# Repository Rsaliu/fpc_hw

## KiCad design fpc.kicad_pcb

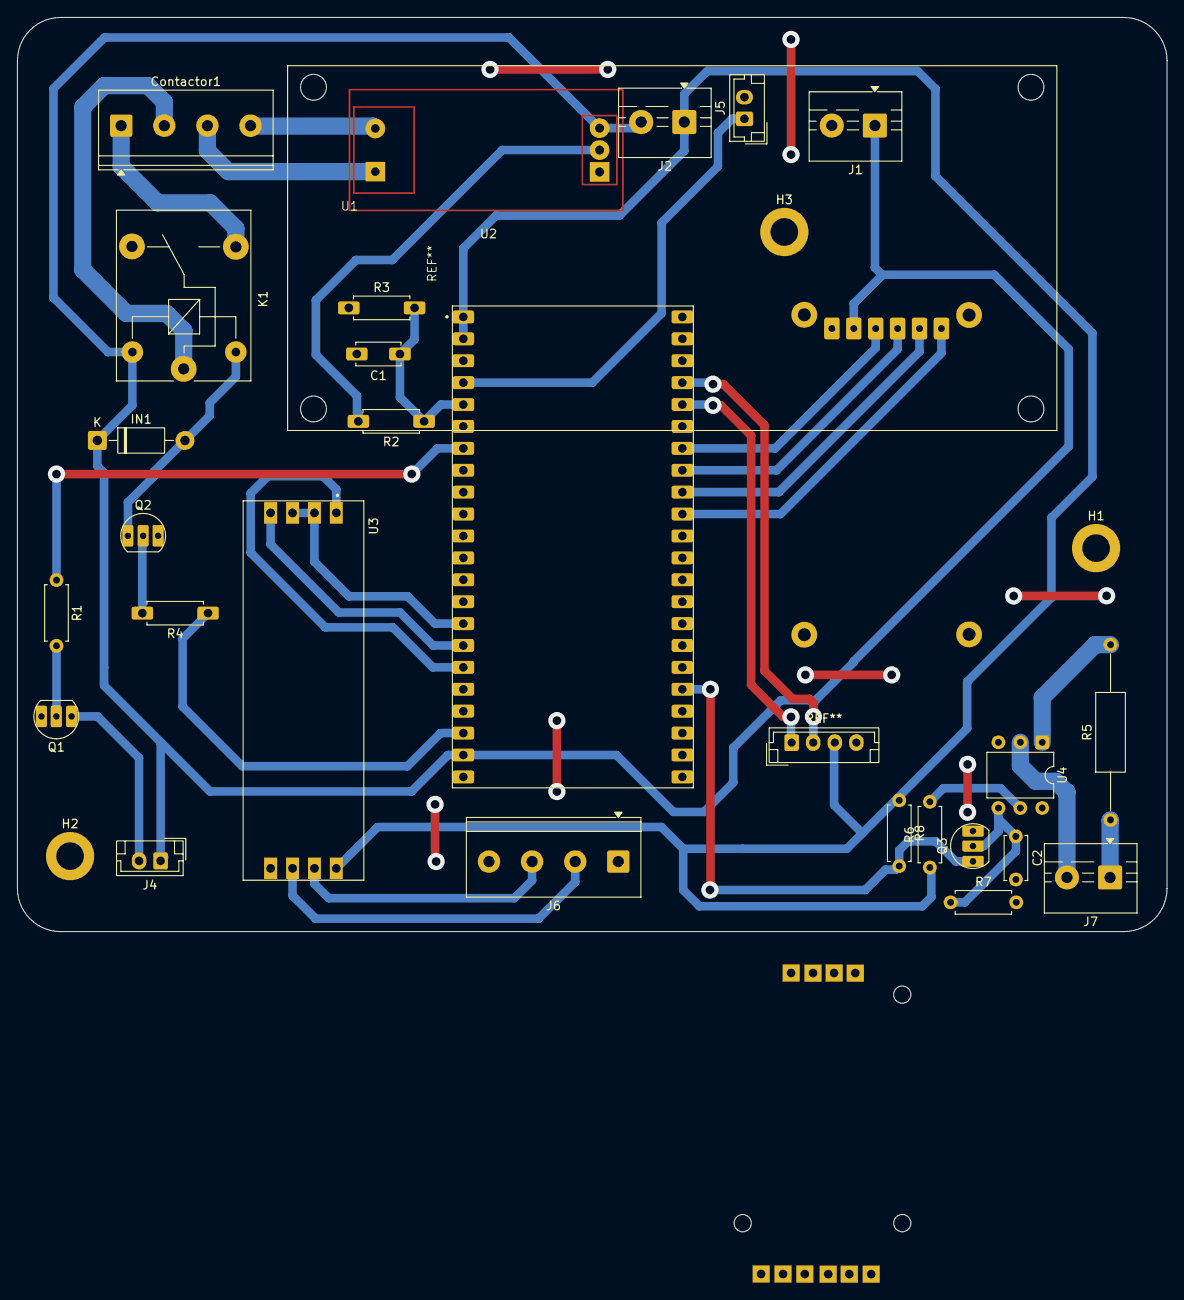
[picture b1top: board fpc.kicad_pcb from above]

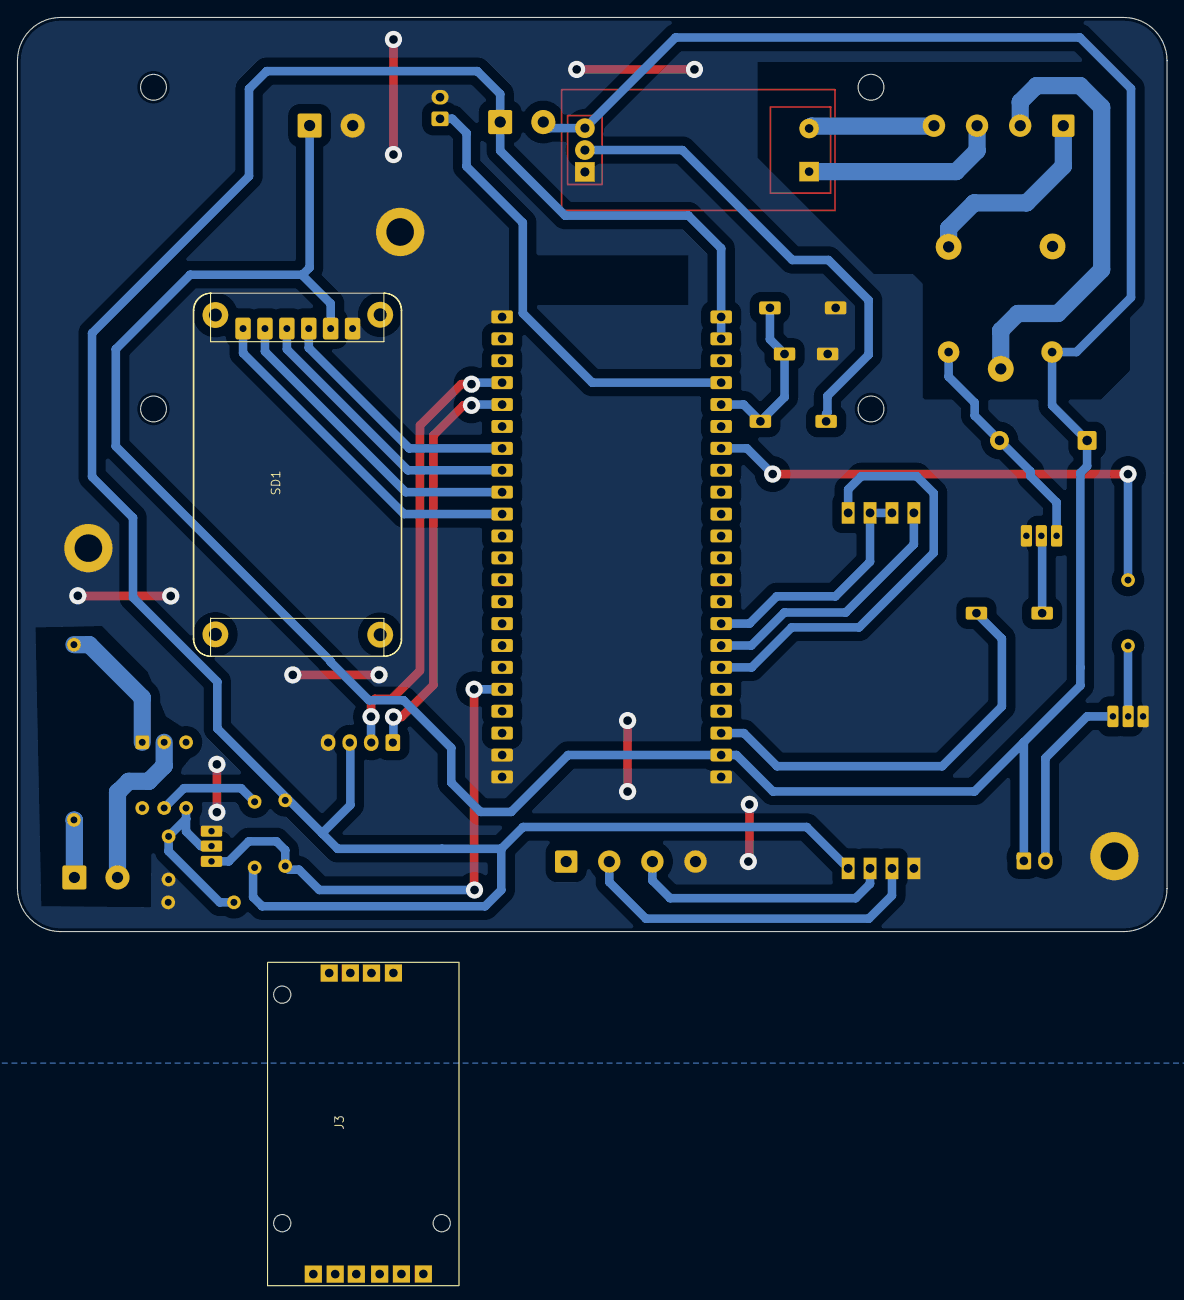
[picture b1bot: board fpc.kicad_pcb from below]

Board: 2 copper layers, 133.3 x 106.0 mm, 31 parts (2 on the bottom side), 33 nets.

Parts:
C1: 100n; C_Disc_D5.0mm_W2.5mm_P5.00mm
C2: 100u; C_Disc_D5.0mm_W2.5mm_P5.00mm
Contactor1: Screw_Terminal_01x04; TerminalBlock_Phoenix_PT-1,5-4-5.0-H_1x04_P5.00mm_Horizontal
H1, H2, H3: MountingHole_Pad; MountingHole_3.2mm_M3_DIN965_Pad
IN1: D; D_DO-41_SOD81_P10.16mm_Horizontal
J1, J7: 15v; TerminalBlock_MaiXu_MX126-5.0-02P_1x02_P5.00mm
J2: Screw_Terminal_01x02; TerminalBlock_MaiXu_MX126-5.0-02P_1x02_P5.00mm
J3: Conn_01x06_Socket; Untitled
J4: BUZZER; JST_EH_B2B-EH-A_1x02_P2.50mm_Vertical
J5: Conn_01x02_Socket; JST_EH_B2B-EH-A_1x02_P2.50mm_Vertical
J6: Screw_Terminal_01x04; TerminalBlock_Phoenix_PT-1,5-4-5.0-H_1x04_P5.00mm_Horizontal
K1: Relay_SPDT; Relay_SPDT_SANYOU_SRD_Series_Form_C
Q1, Q2, Q3: BC547; BC547-BOTSGEEK
R1, R4: 220R; R_Axial_DIN0207_L6.3mm_D2.5mm_P7.62mm_Horizontal
R2, R3, R6, R7, R8: 10K; R_Axial_DIN0207_L6.3mm_D2.5mm_P7.62mm_Horizontal
R5: 330K 1/2W; R_Axial_DIN0309_L9.0mm_D3.2mm_P20.32mm_Horizontal
SD1: SD Card Module; SD_Card_Module
U1: ACS712_Current_Sensor
U2: ESP32-S3-DEVKIT-LIPO; ESP32S3-DEVKIT-BOTSGEEK-LOCAL
U3: RS485_TTL_Module; MODULE_MAX485_MODULE_5V_LOGIC_TLL_TO_RS-485_CONVERTER
U4: H11AA1; DIP-6_W7.62mm

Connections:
3.3V: J2.1, J3.2, R6.1, R8.1, U2.3V3 (+3V3), U3.8 (VCC)
+5V: IN1.1 (K), J1.1, J2.2, J4.1, K1.5, SD1.1 (VCC), U1.3 (VCC), U2.5V (+5V)
/BUZZER_NEG_PIN: J4.2, Q1.1 (C)
/BUZZER_PIN: R1.1, U2.7 (GPIO7)
/CHANGE_MODE_BTN: J5.1, U2.4 (GPIO4)
/CS: SD1.6 (CS), U2.38 (GPIO38/LED1)
/Contactor_live_in: Contactor1.2, K1.1
/Contactor_live_out: Contactor1.1, K1.3
/Curr_analog_out1: R2.2, U1.2 (OUT)
/DRI: U2.9 (GPIO9), U3.2 (RE), U3.3 (DE)
/DS3231_SCL: J3.3, U2.1 (GPIO1)
/DS3231_SDA: J3.4, U2.2 (GPIO2)
/MAINS_DETECT: Q3.1 (C), R8.2, U2.21 (GPIO21)
/MISO: SD1.5 (MISO), U2.41 (GPIO41)
/MOSI: SD1.2 (MOSI), U2.40 (GPIO40)
/Pump_live_in: Contactor1.3, U1.6 (IP+(I_in))
/Pump_live_out: Contactor1.4, U1.5 (IP_-(I_Out))
/RELAY_1: R4.1, U2.14 (GPIO14)
/RS485_A: J6.2, U3.6 (A)
/RS485_B: J6.3, U3.7 (B)
/RX_PIN: U2.11 (GPIO11/FSPID/SPI3_MOSI), U3.1 (R0)
/SCK: SD1.3 (SCK), U2.39 (GPIO39)
/TX_PIN: U2.10 (GPIO10/FSPICS0/SPI3_CS0), U3.4 (DI)
GND: C1.2, C2.2, H1.1 (1_1), H2.1 (1_1), H3.1 (1_1), J1.2, J3.1, J5.2, J6.4, Q1.3 (E), Q2.3 (E), Q3.3 (E), R3.1, R7.2, SD1.4 (GND), U1.1 (GND), U2.GND, U3.5 (GND)
unnamed: IN1.2 (A), K1.2, Q2.1 (C)
unnamed: J7.1, R5.1
unnamed: J7.2, U4.2
unnamed: Q1.2 (B), R1.2
unnamed: Q2.2 (B), R4.2
unnamed: C2.1, Q3.2 (B), R7.1, U4.4
unnamed: R5.2, U4.1
unnamed: R6.2, U4.5
unnamed: C1.1, R2.1, R3.2, U2.5 (GPIO5/PWR_SENS)

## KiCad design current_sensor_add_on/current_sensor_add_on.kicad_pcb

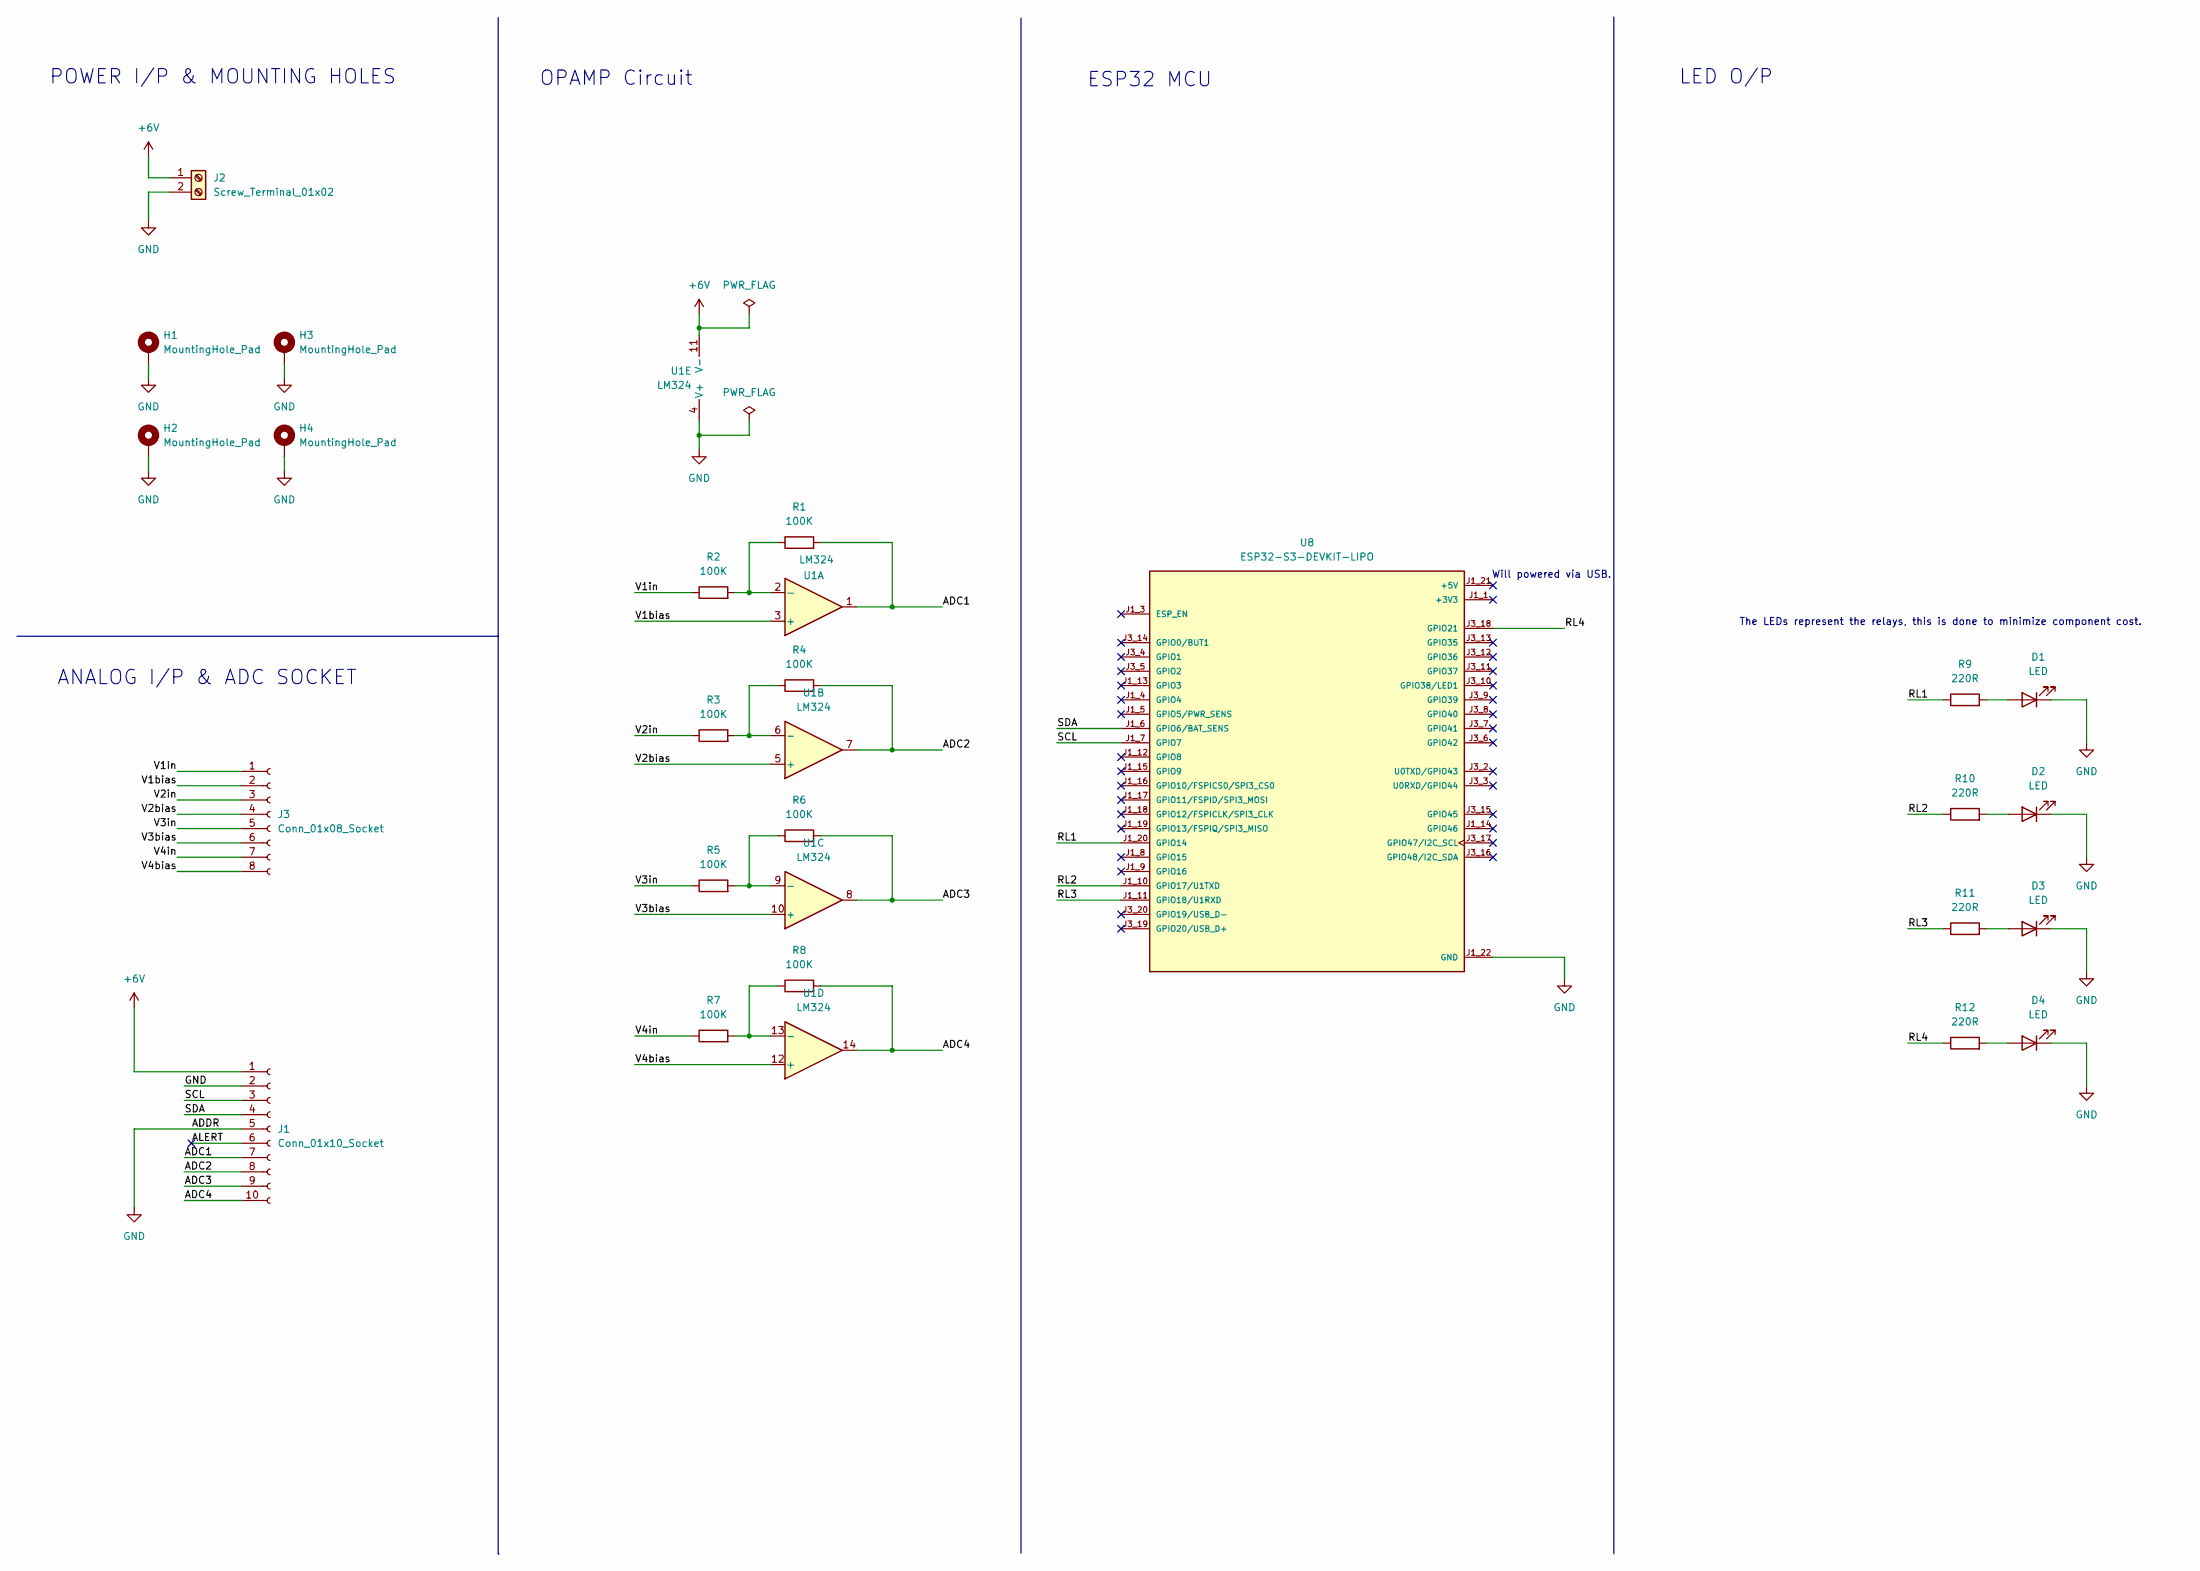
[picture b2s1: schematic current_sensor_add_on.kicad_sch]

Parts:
D1, D2, D3, D4: LED; LED_D4.0mm
H1, H2, H3, H4: MountingHole_Pad; MountingHole_3.2mm_M3_Pad
J1: Conn_01x10_Socket; PinSocket_1x10_P2.54mm_Vertical
J2: Screw_Terminal_01x02; TerminalBlock_CUI_TB007-508-02_1x02_P5.08mm_Horizontal
J3: Conn_01x08_Socket; PinHeader_1x08_P2.54mm_Vertical
R1, R2, R3, R4, R5, R6, R7, R8: 100K; R_Axial_DIN0207_L6.3mm_D2.5mm_P15.24mm_Horizontal
R9, R10, R11, R12: 220R; R_Axial_DIN0207_L6.3mm_D2.5mm_P15.24mm_Horizontal
U1: LM324; DIP-14_W7.62mm_Socket_LongPads
U8: ESP32-S3-DEVKIT-LIPO; XCVR_ESP32-S3-DEVKIT-LIPO; PARTREV B

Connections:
+6V: J1.1, J2.1, U1.11 (V-)
/ADC1: J1.7, R1.2, U1.1
/ADC2: J1.8, R4.2, U1.7
/ADC3: J1.9, R6.2, U1.8
/ADC4: J1.10, R8.2, U1.14
/ALERT: J1.6
/RL1: R9.1, U8.J1_20 (GPIO14)
/RL2: R10.1, U8.J1_10 (GPIO17/U1TXD)
/RL3: R11.1, U8.J1_11 (GPIO18/U1RXD)
/RL4: R12.1, U8.J3_18 (GPIO21)
/SCL: J1.3, U8.J1_7 (GPIO7)
/SDA: J1.4, U8.J1_6 (GPIO6/BAT_SENS)
/V1bias: J3.2, U1.3 (+)
/V1in: J3.1, R2.1
/V2bias: J3.4, U1.5 (+)
/V2in: J3.3, R3.1
/V3bias: J3.6, U1.10 (+)
/V3in: J3.5, R5.1
/V4bias: J3.8, U1.12 (+)
/V4in: J3.7, R7.1
GND: D1.1 (K), D2.1 (K), D3.1 (K), D4.1 (K), H1.1 (1_1), H2.1 (1_1), H3.1 (1_1), H4.1 (1_1), J1.2, J1.5, J2.2, U1.4 (V+), U8.J1_22 (GND), U8.J3_1 (GND), U8.J3_21 (GND), U8.J3_22 (GND)
unnamed: D1.2 (A), R9.2
unnamed: D2.2 (A), R10.2
unnamed: D3.2 (A), R11.2
unnamed: D4.2 (A), R12.2
unnamed: R1.1, R2.2, U1.2 (-)
unnamed: R3.2, R4.1, U1.6 (-)
unnamed: R5.2, R6.1, U1.9 (-)
unnamed: R7.2, R8.1, U1.13 (-)

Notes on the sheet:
ESP32 MCU
OPAMP Circuit
Will powered via USB.
LED O/P
POWER I/P & MOUNTING HOLES
The LEDs represent the relays, this is done to minimize component cost.
ANALOG I/P & ADC SOCKET

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
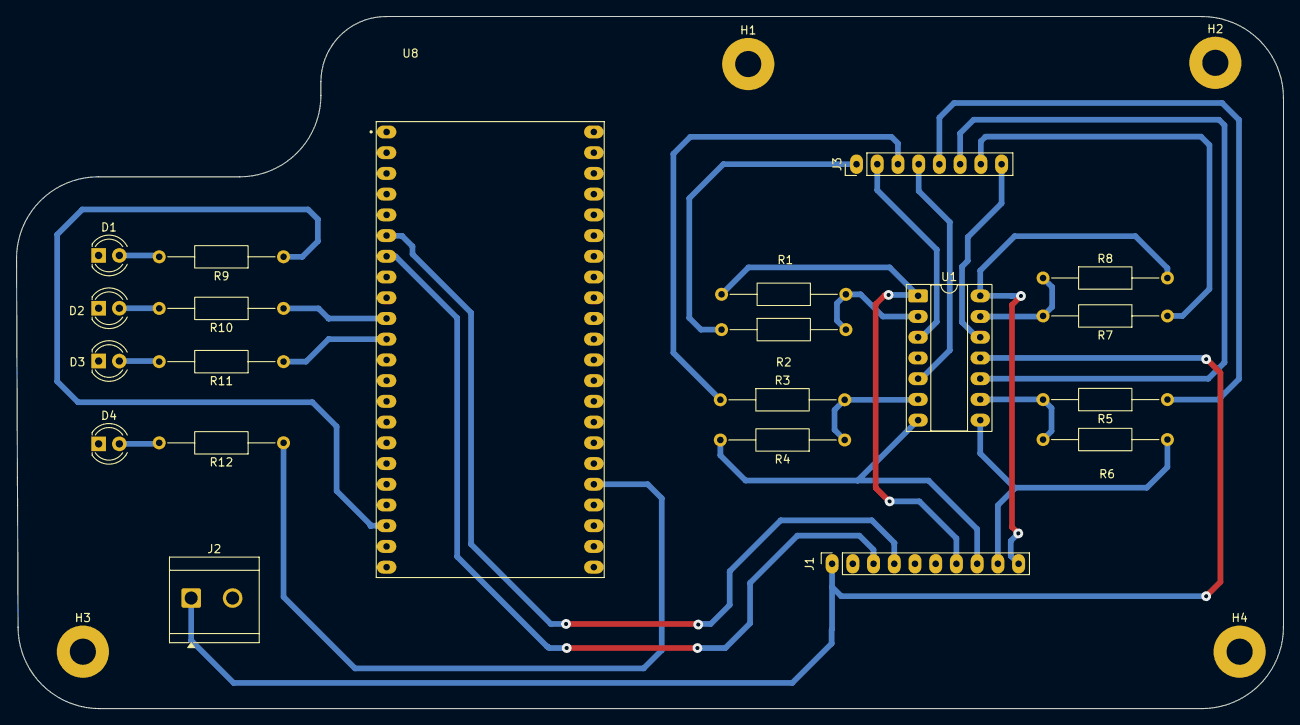
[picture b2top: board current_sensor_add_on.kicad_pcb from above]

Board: 2 copper layers, 155.3 x 84.8 mm, 25 parts (0 on the bottom side), 28 nets.

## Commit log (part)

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2025-06-24 just startup files
2025-06-26 just added a file
2025-06-30 fpc power supply
2025-06-30 Level Sensor Subsheet added
2025-06-30 kicad version 9.0 schematic
2025-06-30 esp32 devkit
2025-07-01 led changes
2025-07-01 sample
2025-07-01 added mcu directly to the fpc project
2025-07-01 relay subsheet
2025-07-01 current sensor schematic
2025-07-02 mcu footprint
2025-07-02 Pin label and notes
2025-07-02 added label on the capacitors and added diode to the 5v regulator for reverse polarity
2025-07-03 updated the schematic diagram
2025-07-03 merged power schematics to main
2025-07-03 Add mcu schematic
2025-07-03 Add library directory and mcu footprints
2025-07-03 relay schematic
2025-07-03 relay schematic upload
2025-07-03 level sensor updates
2025-07-03 Current schematic update to main
2025-07-04 adding level sensor schematic, and adding footprints and symbols for level sensor and current sensor
2025-07-04 add current sensor schematic
2025-07-16 fpc_hw schematic
2025-07-18 schematic_merged
2025-07-25 new update of schematic and pcb
2025-09-29 latest update
2025-12-01 [alert_pin_update] Adding alert pin to project
2025-12-01 [alert_pin_update] GPIO changed
